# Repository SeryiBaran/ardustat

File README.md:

# Ardustat

Термостат на Arduino Nano + NTC с 4-разрядным 7-сегментным дисплеем.

Схема:

Схема в KiCad [здесь](./kicad).

Схема KiCad в PDF [здесь](./kicad/renders/scheme.pdf).

ВНИМАНИЕ!!! Код создавался в онлайн-симуляторе [Wokwi](https://wokwi.com/) и не проверялся в реальности.

Настройки сохраняются в EEPROM. Беспокоиться не стоит, используется библиотека EEManager с удобной логикой.

Занятые ресурсы МК по мнению PlatformIO:

```
RAM:   [=         ]  10.0% (used 205 bytes from 2048 bytes)
Flash: [==        ]  24.7% (used 7586 bytes from 30720 bytes)
```

## Зависимости - в [platformio.ini](./platformio.ini)

## Электронные компоненты

- Arduino Nano
- Реле на 5V на ток `мощность / напряжение` + запас. Например ТЭН на 2КВт с напряжением 220V потребляет ток ~9A - лучше взять реле с запасом, например на 16 ампер. На али лично я не видел модулей реле выше 10 ампер, поэтому можно взять твердотельное. Но оно существенно дороже обычного - 500 рублей против 60. Зато оно не боится частых переключений, не нужна никакая обвязка, контакты не могут износиться (их там нет -_-). Минус твердотельного реле - оно греется, поэтому нужно брать с запасом по току и/или крепить на радиатор
- Модуль энкодера с кнопкой с обвязкой против дребезга ([инфо](https://github.com/GyverLibs/EncButton#%D1%80%D0%B5%D0%BA%D0%BE%D0%BC%D0%B5%D0%BD%D0%B4%D0%B0%D1%86%D0%B8%D0%B8)). На али у него круглая синяя плата
- Термистор
- Резистор, равный сопротивлению термистора
- Дисплей TM1637

## Руководство пользователя

В формате .Docx - в нем удобнее делать дизайн для печати.

Приложено к Github релизу и [лежит тут](./USER_MANUAL.docx)

## А как прошить, а как собрать

- [Уроки Arduino](https://alexgyver.ru/arduino-first/)
- [Оф гайд Platformio CLI](https://docs.platformio.org/en/latest/core/quickstart.html)
- [Оф гайд Platformio IDE (VSCode)](https://docs.platformio.org/en/latest/integration/ide/vscode.html)

## История версий - в [CHANGELOG.md](./CHANGELOG.md)

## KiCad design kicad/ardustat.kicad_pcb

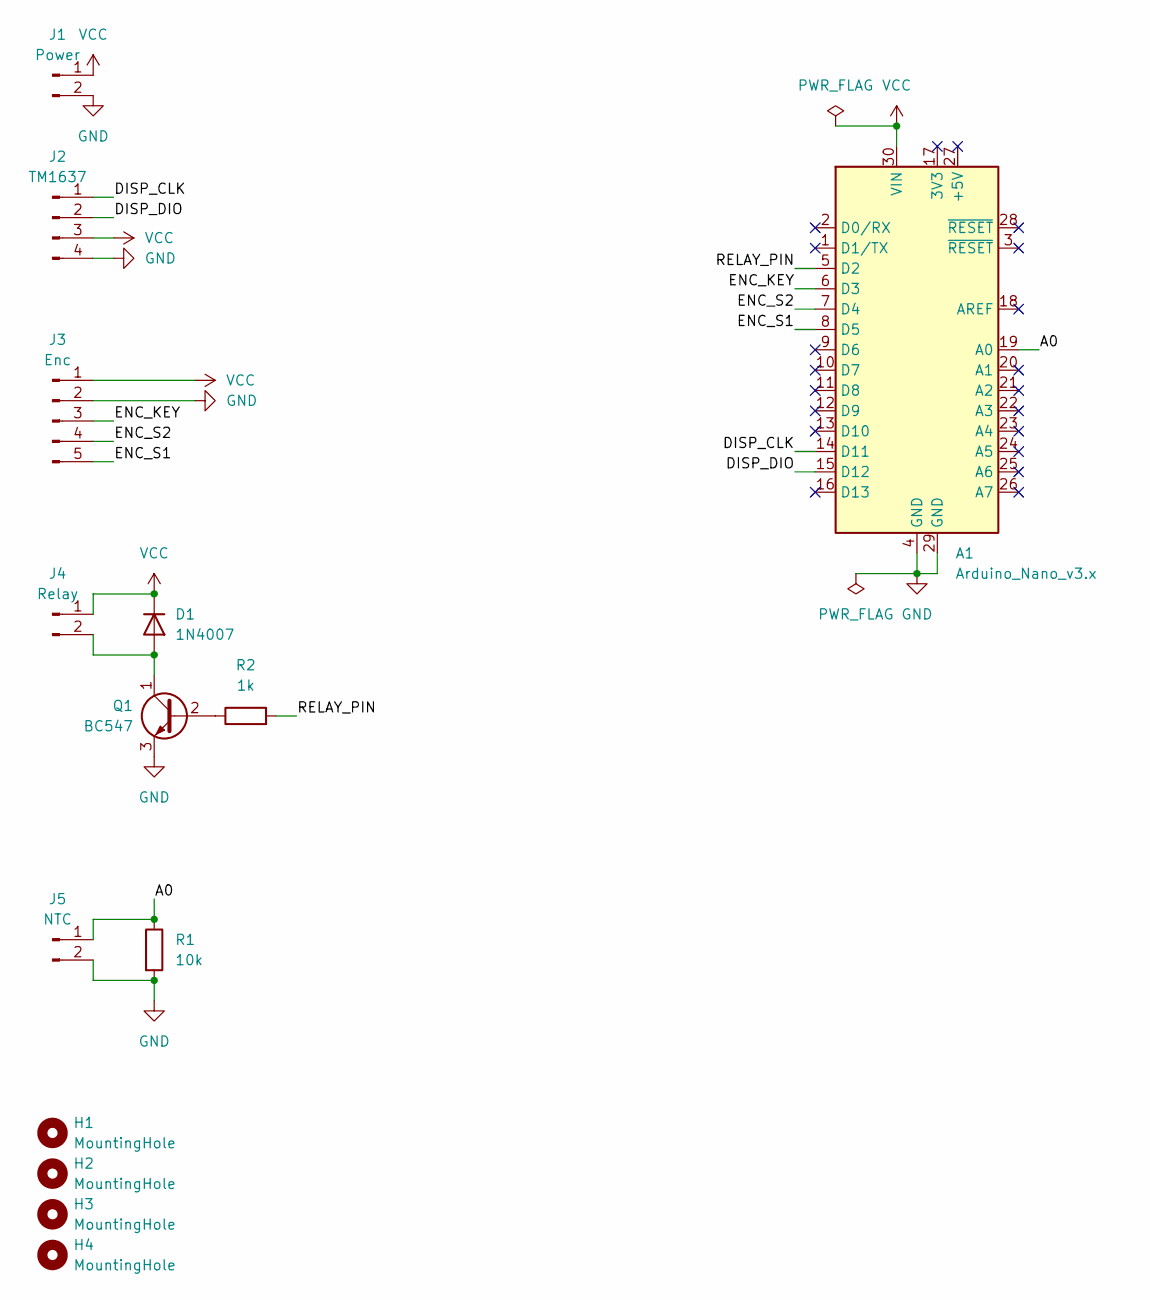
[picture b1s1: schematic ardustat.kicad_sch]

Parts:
A1: Arduino_Nano_v3.x; Arduino_Nano
D1: 1N4007; D_DO-41_SOD81_P10.16mm_Horizontal
H1, H2, H3, H4: MountingHole; MountingHole_3.2mm_M3_DIN965_Pad
J1: Power; PinHeader_1x02_P2.54mm_Vertical
J2: TM1637; PinHeader_1x04_P2.54mm_Vertical
J3: Enc; PinHeader_1x05_P2.54mm_Vertical
J4: Relay; PinHeader_1x02_P2.54mm_Vertical
J5: NTC; PinHeader_1x02_P2.54mm_Vertical
Q1: BC547; TO-92_Inline
R1: 10k; R_Axial_DIN0207_L6.3mm_D2.5mm_P10.16mm_Horizontal
R2: 1k; R_Axial_DIN0207_L6.3mm_D2.5mm_P10.16mm_Horizontal

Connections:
/A0: A1.19 (A0), J5.1, R1.1
/DISP_CLK: A1.14 (D11), J2.1
/DISP_DIO: A1.15 (D12), J2.2
/ENC_KEY: A1.6 (D3), J3.3
/ENC_S1: A1.8 (D5), J3.5
/ENC_S2: A1.7 (D4), J3.4
/RELAY_PIN: A1.5 (D2), R2.2
GND: A1.4 (GND), A1.29 (GND), J1.2, J2.4, J3.2, J5.2, Q1.3 (E), R1.2
unnamed: D1.2 (A), J4.2, Q1.1 (C)
unnamed: Q1.2 (B), R2.1
VCC: A1.30 (VIN), D1.1 (K), J1.1, J2.3, J3.1, J4.1

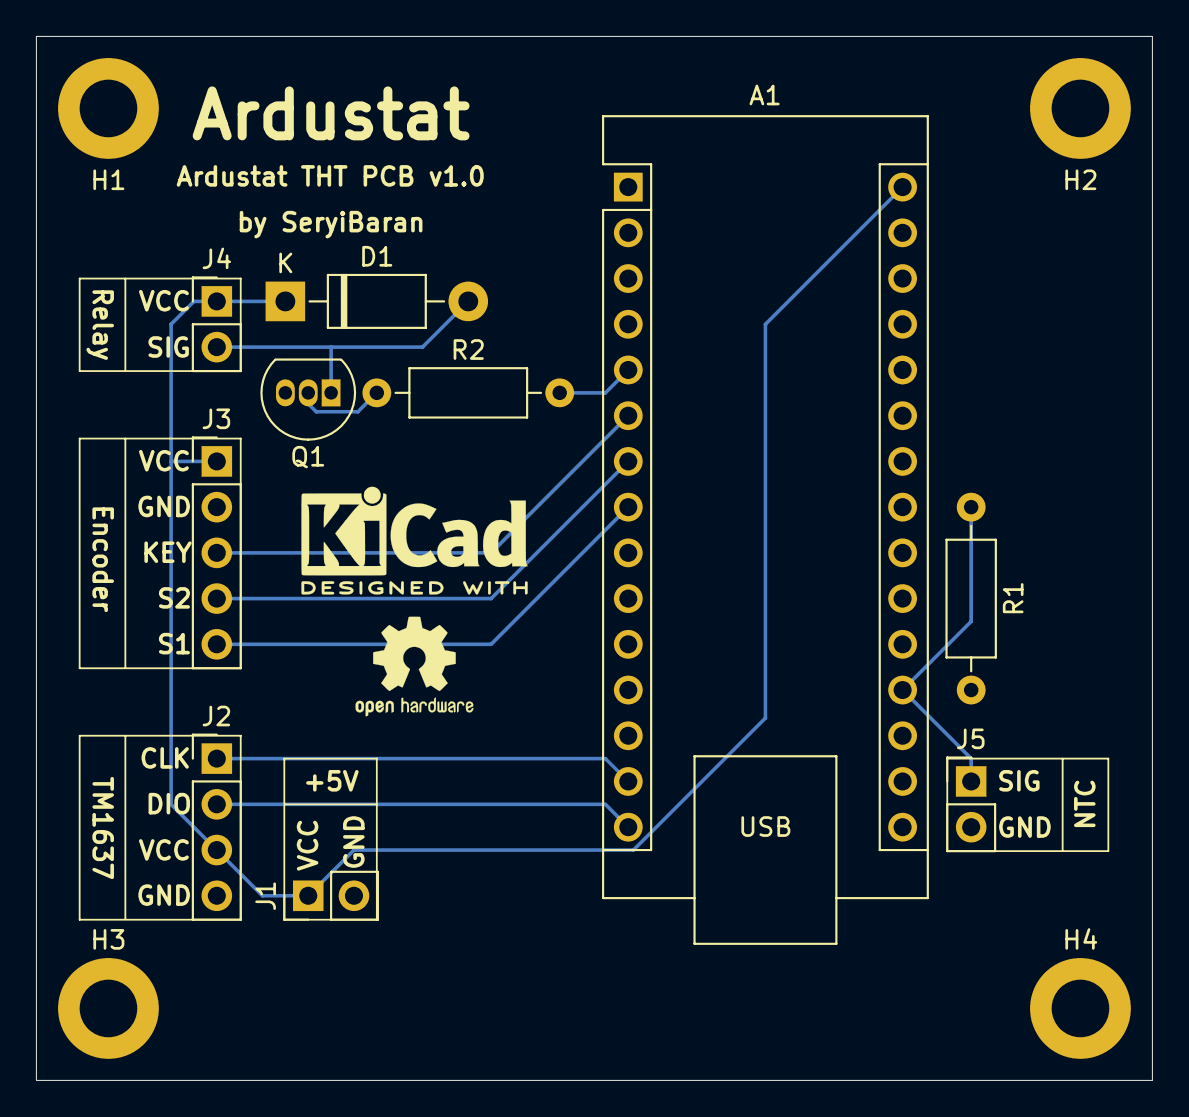
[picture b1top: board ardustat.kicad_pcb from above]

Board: 2 copper layers, 62.0 x 58.0 mm, 14 parts (0 on the bottom side), 11 nets.

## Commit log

2023-12-09 Init commit
2023-12-09 remove ".obsidian" dir
2023-12-09 add ".obsidian" dir to gitignore
2023-12-09 fix fritzing image path in readme
2023-12-09 add "Электронные компоненты" in readme
2023-12-09 remove unused variable
2023-12-09 edit manual
2023-12-09 platformio
2023-12-09 move libs from "lib" in repo to platformio manager
2023-12-09 create func "load_settings"
2023-12-09 use EEManager
2023-12-09 upd readme
2023-12-09 readme: add links to arduino guide and platformio guide
2023-12-10 v1.1.0
2023-12-10 loop code optimize
2023-12-10 optimize
2023-12-10 readme: add relay info
2023-12-10 remove bad comment
2023-12-10 v1.1.1
2023-12-10 upd manual
2023-12-12 reformat with google style
2023-12-12 format comments
2023-12-12 reformat comments again -_-
2023-12-14 docs: changelog style improve
2023-12-14 docs: improve changelog
2023-12-14 style: add editorconfig
2024-03-11 feat: display auto off
2024-06-16 kicad
